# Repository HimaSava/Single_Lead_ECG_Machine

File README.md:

# Single_Lead_ECG_Machine

This project started as the project component for my subject analog electronic communcation that I took in my Winter Sem 2019.

The project uses 3 wires to be connected to the paitent as to aquire the ECG waveform from 2 of them and the third used as ground. The Circuit uses basic filteration techniques to get rid of the surrounding noise and amplify the signal to be effectively seen on a osciloscope.

## Components of the Circuit and thier purpose:
#### 1. Instrumentational Amplifier:
The ECG signal received from the body is in milivolts and thus needs to be amplified in order to be captured by any instrument. An instrumentational amplifier is used rather than an normal amplifier as it helps limit the noise entering the system due to its differential amplification functionality.

#### 2. High Pass Filter:
A high pass filter is used to get rid of the lower frequencies caught up in the system. This filter also takes care of the dc voltage in the system, avoiding saturation of the furthur amplification stages. An second order filter is used for better results.

#### 3. Low Pass Filter:
A low pass filter as expected is again used to remove the unnecessary frequencies. A second order filter is used for optimised results.

#### 4. Notch Filter:
A notch filter is a filter that helps remove a very narrow band of frequencies. In our case it is tuned for 50Hz. This is the standard AC freq. in the Indian power supply and thus is present in the surrounding in great quantities. This is caught in the system and can lead to distorting the final waveform significantly.

## Components used:
#### 1. OpAmps TL074CN (Highly advised for this experiment)
#### 2. Registers 
#### 3. Bi-Directional Capacitors(Ensure the cap are not uni-directional as the ECG signal is bi-directional)

## Tools used:
1. Multisim - To design and test the basic circuit.
2. Eagle AutoCAD - To design the custom PCB and help design the soldering breadboard circuit layout.

## Scope for improvement:
#### Currently the waveform is only viewed using an osciloscope, but in future I want to connect the system to my laptop and record data using it. For this a few more components need to be added to the ciruit as listed below:

1. Level Shifter:
An Analog to digital converter can only deal with positive voltages thus the waveform needs to be shifted upwards to convert the negative part of the ECG signal to positive.

2. A2D converter:
An analog to digital converter is needed as our output is analog but the inut by the microcontroller can only be digital.

3. Microcontroller:
An microcontroller will be able to accept the input from the A2D converter and using Communcation protocols as Serial(RS232), ICP, etc transfer the data to the PC.

4. PC end program:
Once we start recieving the data from the circuit it is important to store the same and show the output in the most familier fashion of an graph. This will be handled by an PC end program.

#### A custom designed PCB will also help in reducing the noise in the system.

### Pls find the attached in the folders above:
1. Individual Circuits of the filters
2. The complete Circuit for the ECG.
3. Eagle files for the PCB (Gerber files will be added shortly)
4. Output waveforms captured by the circuit and the final pictures of the circuit.

Manufactured Layout V1.0

Output!!

#### -Himanshu Savargaonkar
##### P.S. Shoutout to Praneeth G (gp201) for being the test subject for all the live tests conducted in the debugging phase :)

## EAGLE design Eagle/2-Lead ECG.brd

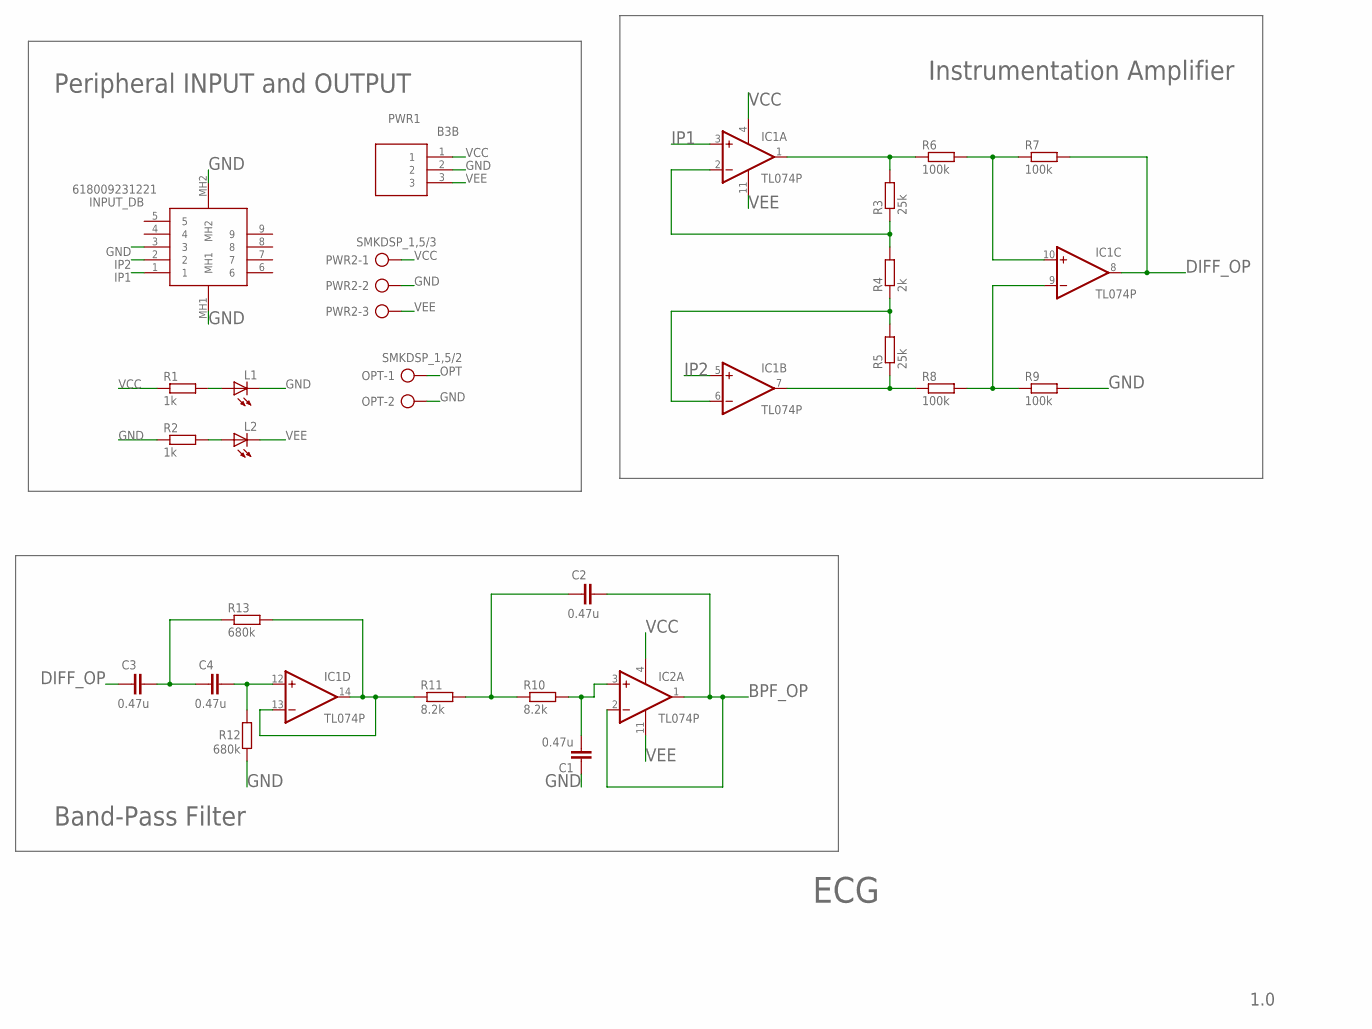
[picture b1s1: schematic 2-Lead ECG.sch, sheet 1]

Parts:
C1, C2, C3, C4: 0.47u; C050-025X075
IC1, IC2: TL074P; DIL14
INPUT_DB: 618009231221
L1, L2: LED3MM
OPT: SMKDSP_1,5/2
PWR1: B3B; SHDR3W64P0X250_1X3_1000X380X60
PWR2: SMKDSP_1,5/3
R1, R2: 1k; 0207/10
R3, R5: 25k; 0204V
R4: 2k; 0207/10
R6, R7, R8, R9: 100k; 0207/10
R10, R11: 8.2k; 0207/10
R12, R13: 680k; 0207/10

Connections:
BPF_OP: C2.2, IC2.1 (OUT), IC2.2 (-IN); also elsewhere on the board
DIFF_OP: C3.1, IC1.8 (OUT), R7.2
GND: C1.1, INPUT_DB.3, INPUT_DB.MH1, INPUT_DB.MH2, L1.K (C), OPT.2, PWR1.2, PWR2.2, R2.1, R9.2, R12.1; also elsewhere on the board
IP1: IC1.3 (+IN), INPUT_DB.1
IP2: IC1.5 (+IN), INPUT_DB.2
unnamed: L1.A, R1.2
unnamed: L2.A, R2.2
unnamed: IC1.1 (OUT), R3.2, R6.1
unnamed: IC1.2 (-IN), R3.1, R4.2
unnamed: IC1.6 (-IN), R4.1, R5.2
unnamed: IC1.7 (OUT), R5.1, R8.1
unnamed: IC1.10 (+IN), R6.2, R7.1
unnamed: IC1.9 (-IN), R8.2, R9.1
unnamed: C3.2, C4.1, R13.1
unnamed: IC1.13 (-IN), IC1.14 (OUT), R11.1, R13.2
unnamed: C4.2, IC1.12 (+IN), R12.2
unnamed: C2.1, R10.1, R11.2
unnamed: C1.2, IC2.3 (+IN), R10.2
OPT: OPT.1; also elsewhere on the board
VCC: IC1.4 (V+), IC2.4 (V+), PWR1.1, PWR2.1, R1.1; also elsewhere on the board
VEE: IC1.11 (V-), IC2.11 (V-), L2.K (C), PWR1.3, PWR2.3

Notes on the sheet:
Peripheral INPUT and OUTPUT
Instrumentation Amplifier
Band-Pass Filter
1.0
ECG

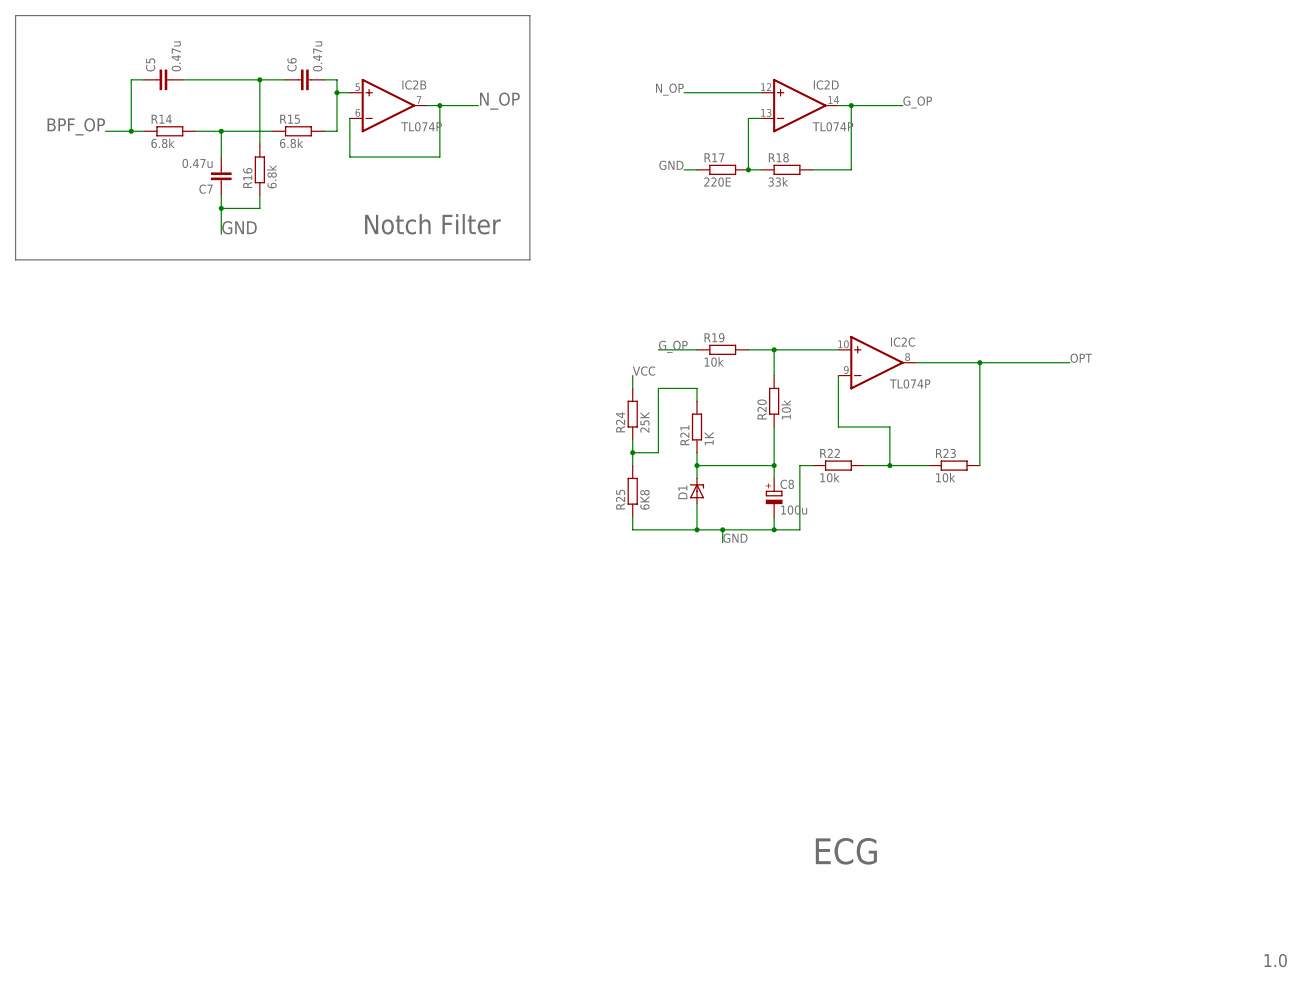
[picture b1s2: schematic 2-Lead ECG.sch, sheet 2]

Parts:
C5, C6, C7: 0.47u; C050-025X075
C8: 100u; E2,5-5
D1: ZENER-DIODEC1702-15; C1702-15
IC2: TL074P; DIL14
R14, R15, R16: 6.8k; 0207/10
R17: 220E; 0204V
R18: 33k; 0204V
R19, R20, R22, R23: 10k; 0204V
R21: 1K; 0207/10
R24: 25K; 0207/10
R25: 6K8; 0207/10

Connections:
BPF_OP: C5.1, R14.1; also elsewhere on the board
GND: C7.1, C8.-, D1.A, R16.1, R17.1, R22.1, R25.1; also elsewhere on the board
G_OP: IC2.14 (OUT), R18.2, R19.1
unnamed: IC2.13 (-IN), R17.2, R18.1
unnamed: C5.2, C6.1, R16.2
unnamed: C6.2, IC2.5 (+IN), R15.2
unnamed: C7.2, R14.2, R15.1
unnamed: IC2.10 (+IN), R19.2, R20.2
unnamed: IC2.9 (-IN), R22.2, R23.1
unnamed: R21.2, R24.1, R25.2
unnamed: C8.+, D1.C, R20.1, R21.1
N_OP: IC2.6 (-IN), IC2.7 (OUT), IC2.12 (+IN)
OPT: IC2.8 (OUT), R23.2; also elsewhere on the board
VCC: R24.2; also elsewhere on the board

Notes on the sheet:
Notch Filter
ECG
1.0

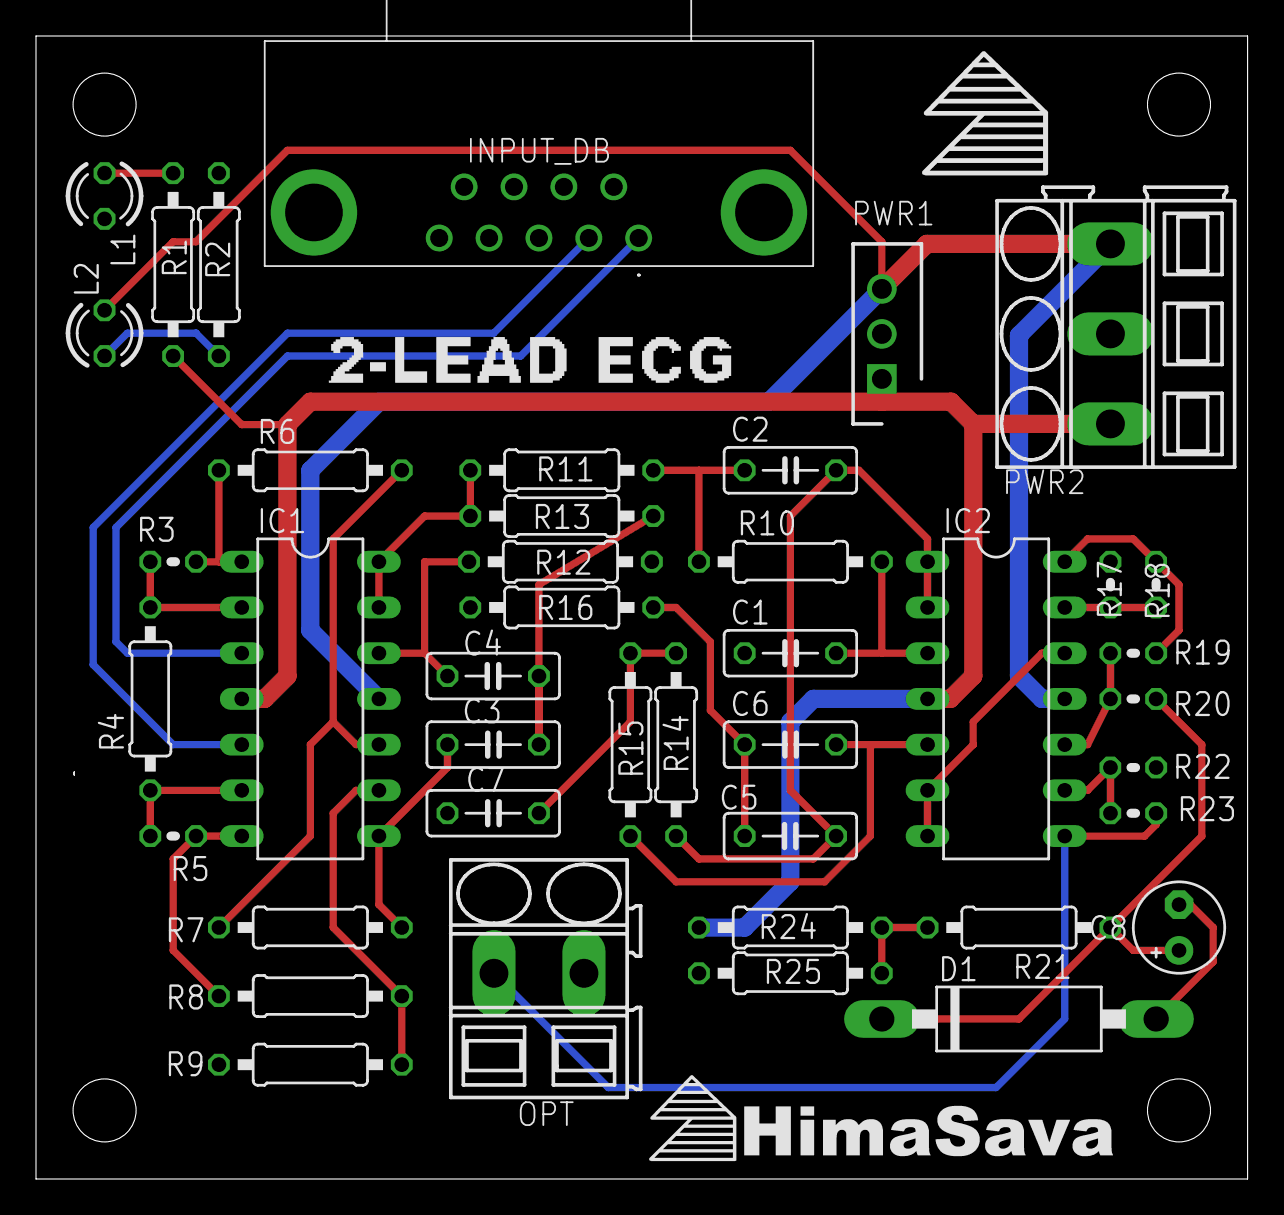
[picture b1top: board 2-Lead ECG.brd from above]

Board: 2 copper layers, 67.3 x 63.5 mm, 42 parts (0 on the bottom side), 31 nets.

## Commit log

2020-09-21 testing merging Eagle files
2020-09-21 Changing stuff in brd
2020-09-21 Changes made to sch file
2021-04-21 Updating Eagle files
